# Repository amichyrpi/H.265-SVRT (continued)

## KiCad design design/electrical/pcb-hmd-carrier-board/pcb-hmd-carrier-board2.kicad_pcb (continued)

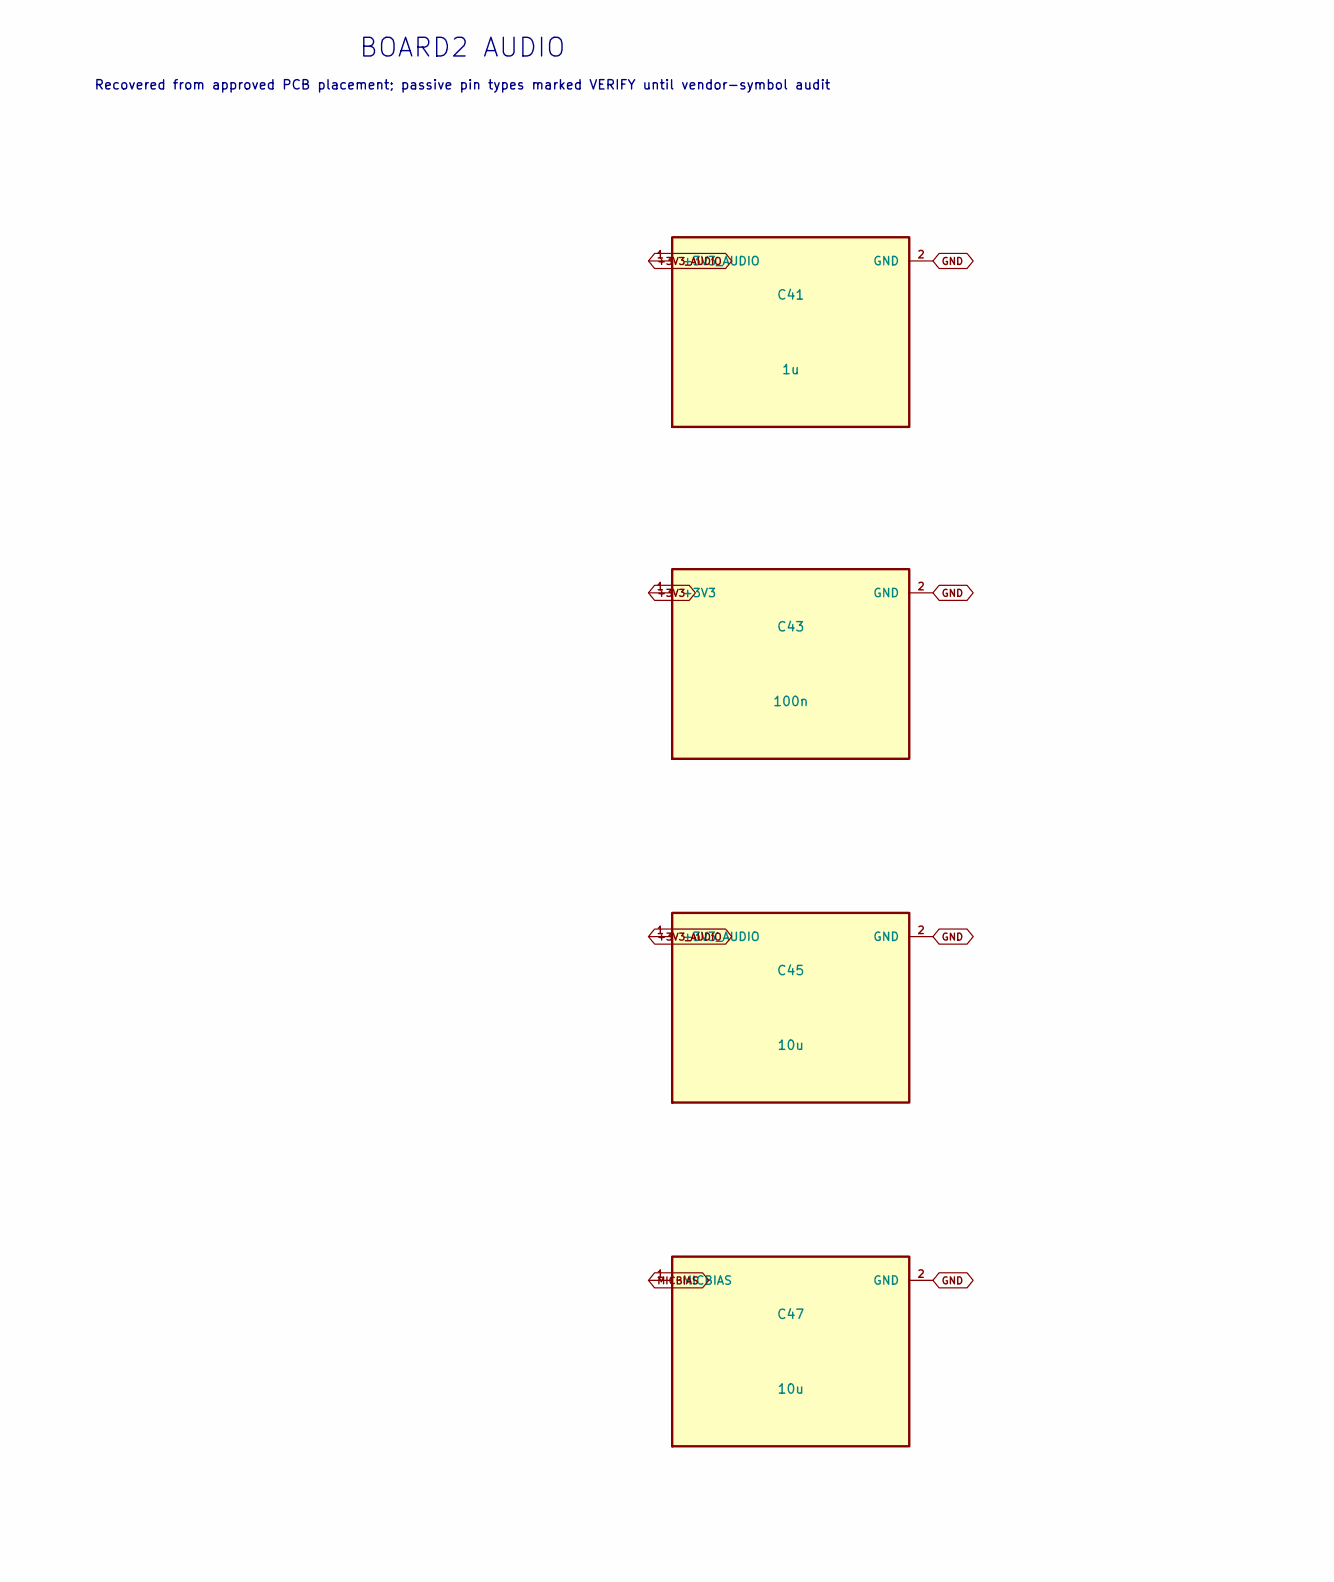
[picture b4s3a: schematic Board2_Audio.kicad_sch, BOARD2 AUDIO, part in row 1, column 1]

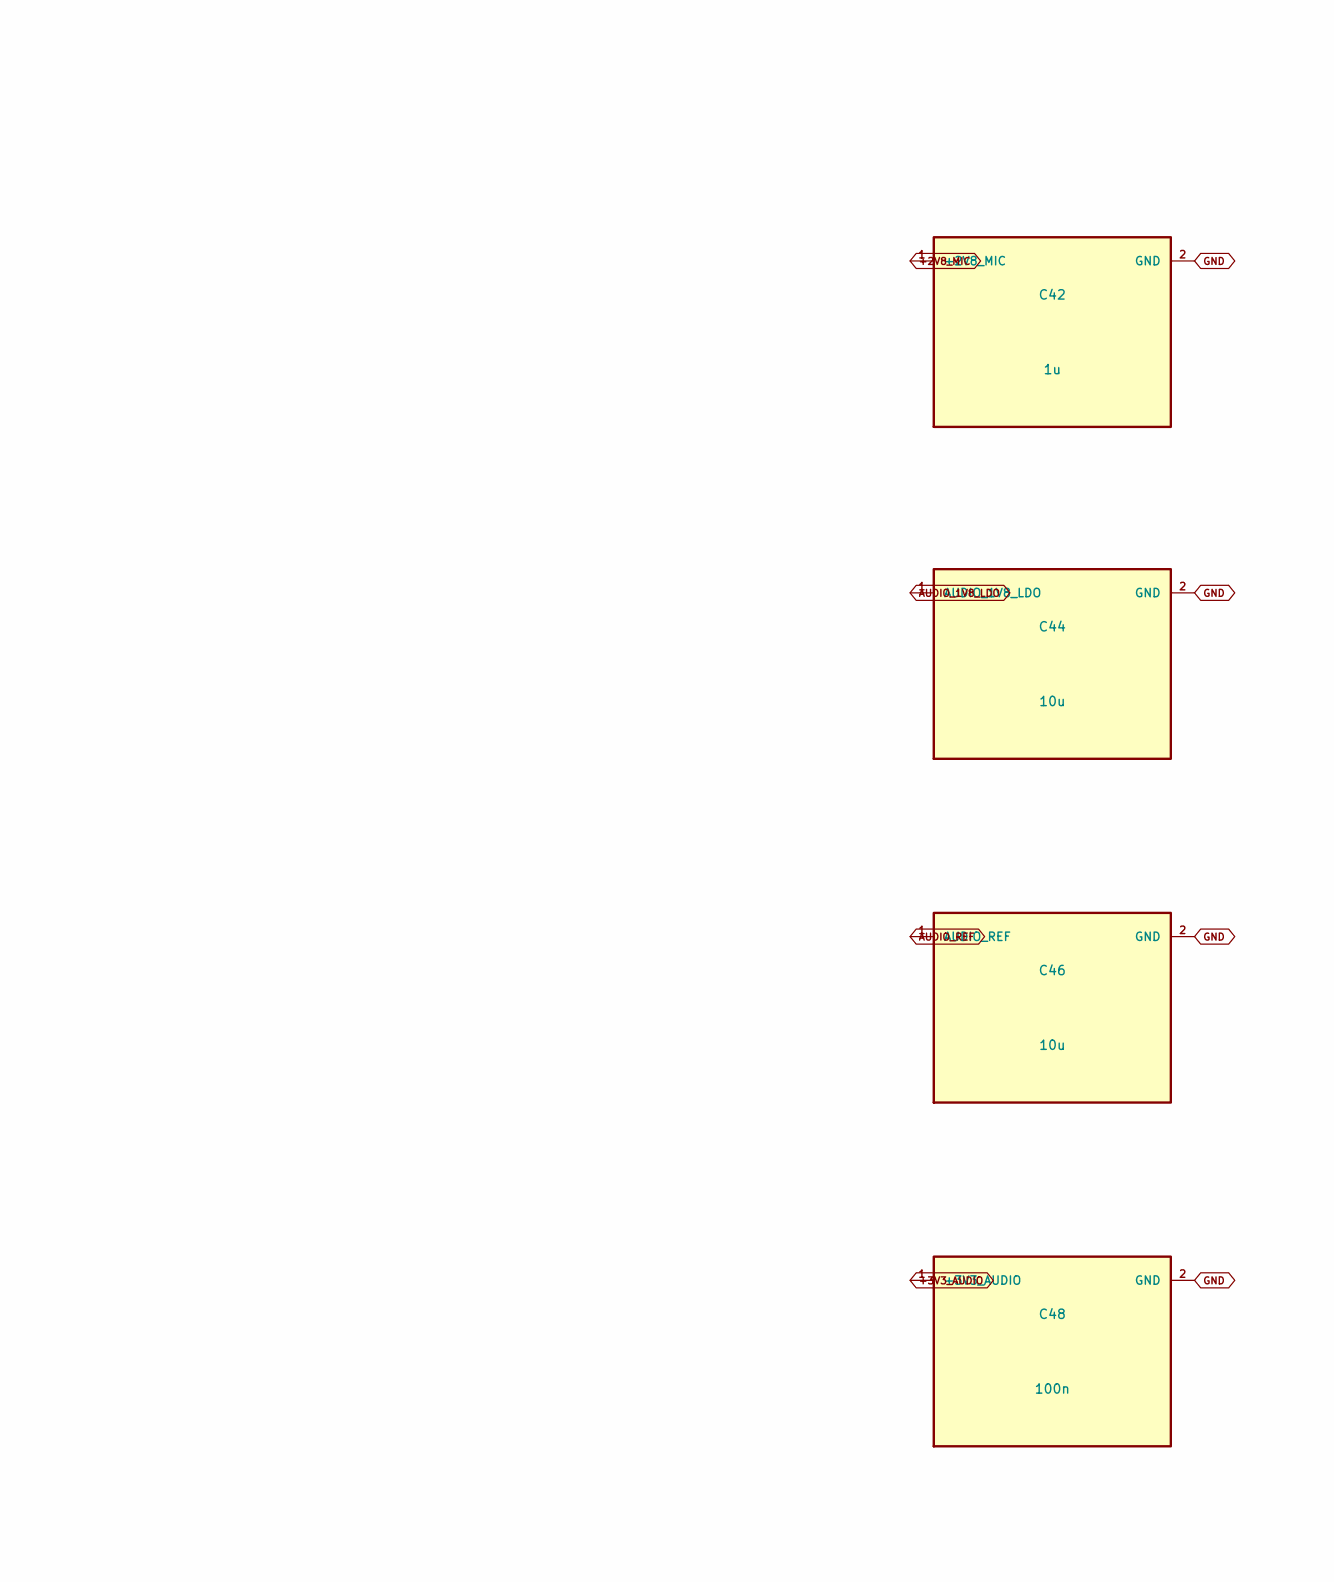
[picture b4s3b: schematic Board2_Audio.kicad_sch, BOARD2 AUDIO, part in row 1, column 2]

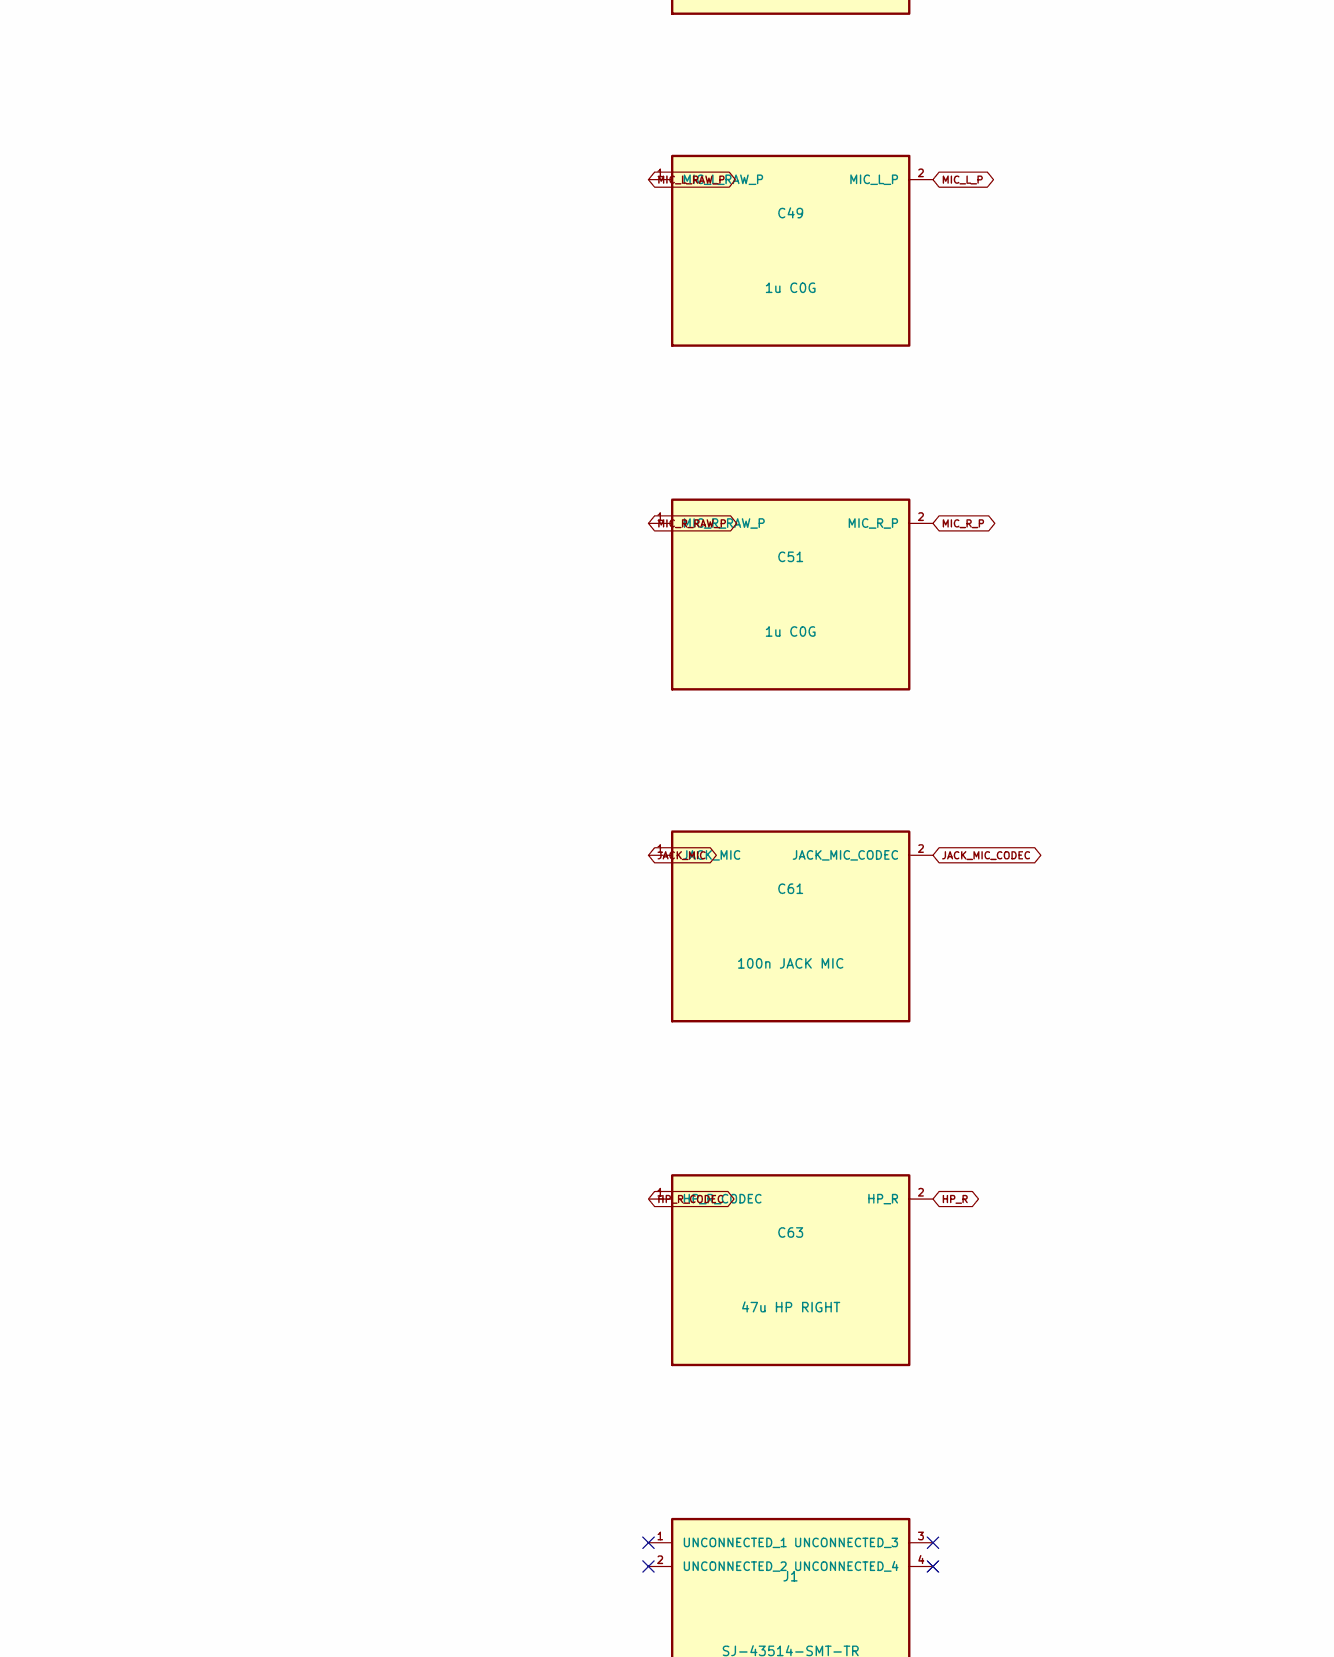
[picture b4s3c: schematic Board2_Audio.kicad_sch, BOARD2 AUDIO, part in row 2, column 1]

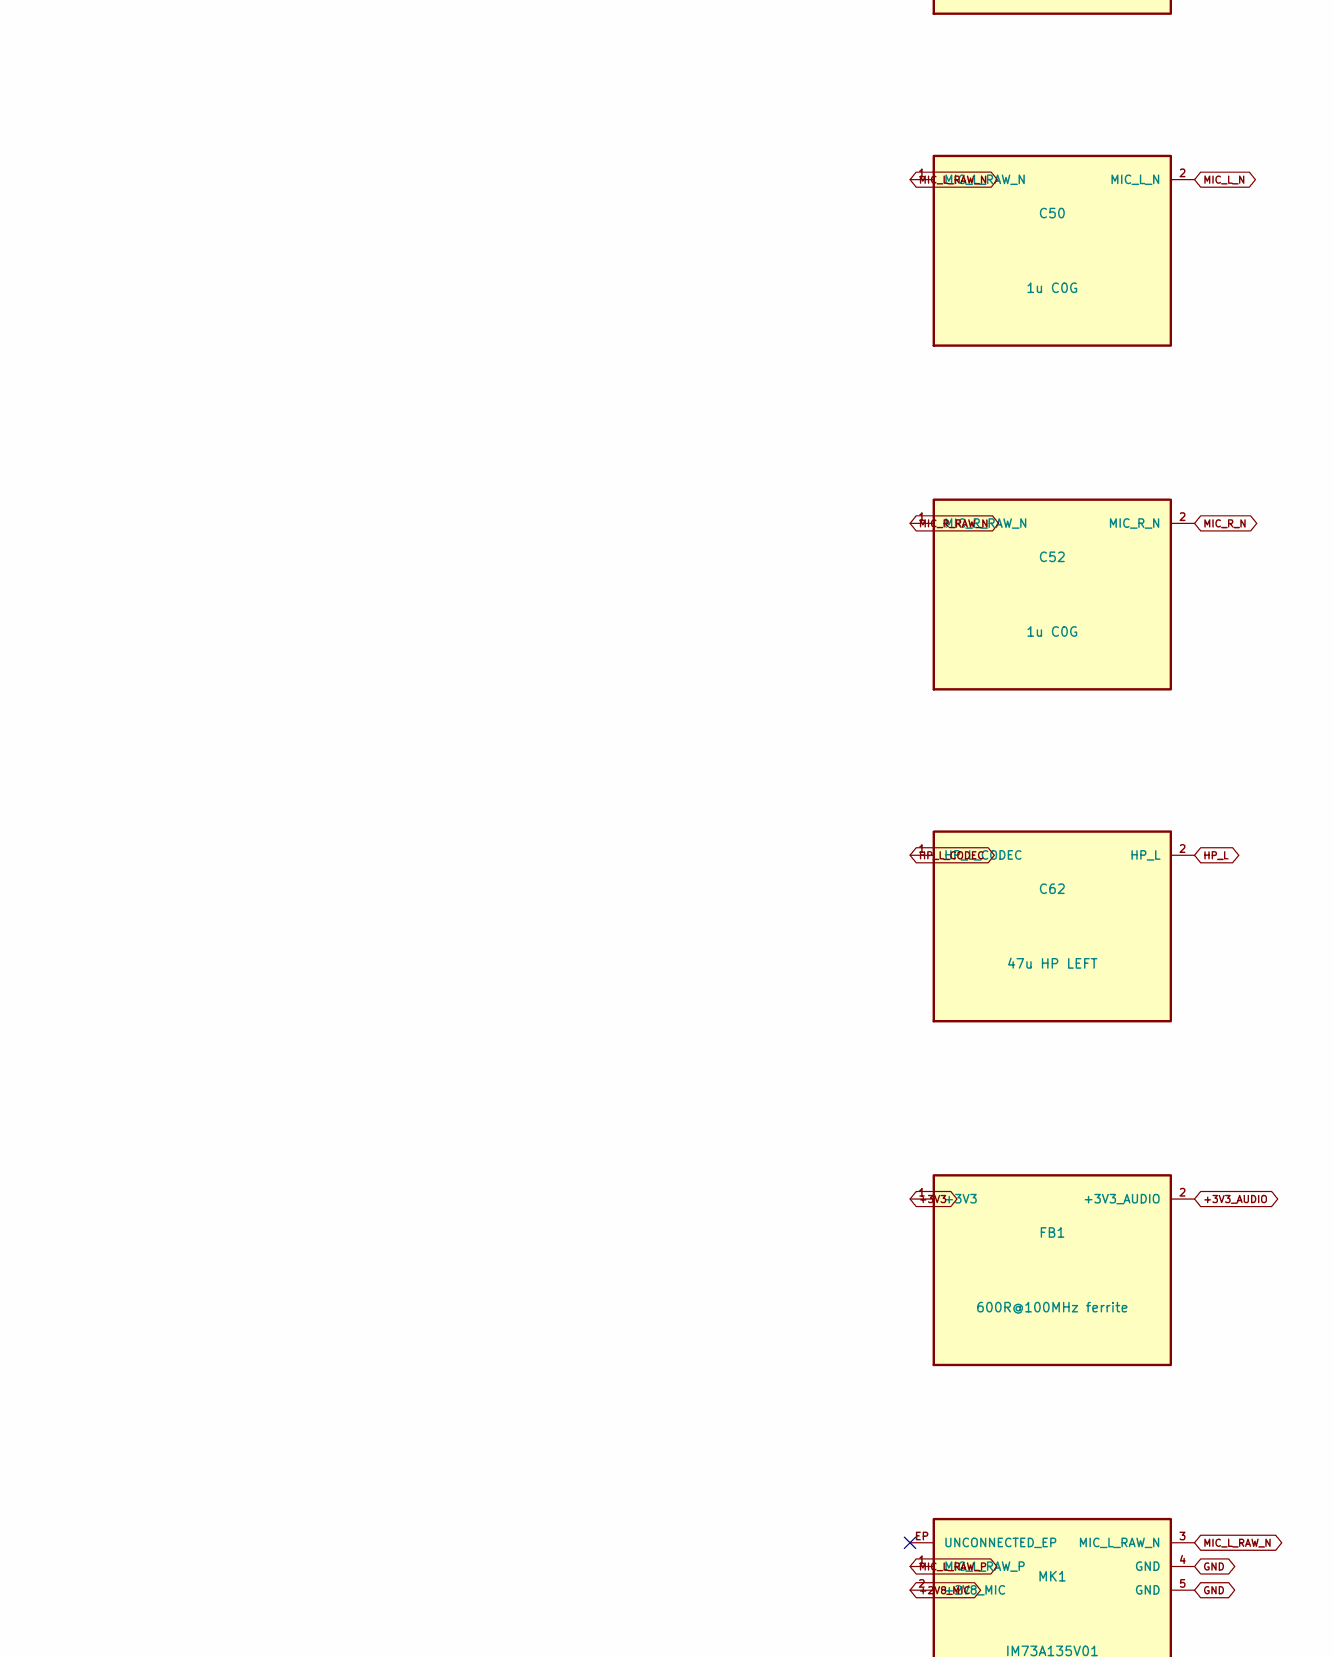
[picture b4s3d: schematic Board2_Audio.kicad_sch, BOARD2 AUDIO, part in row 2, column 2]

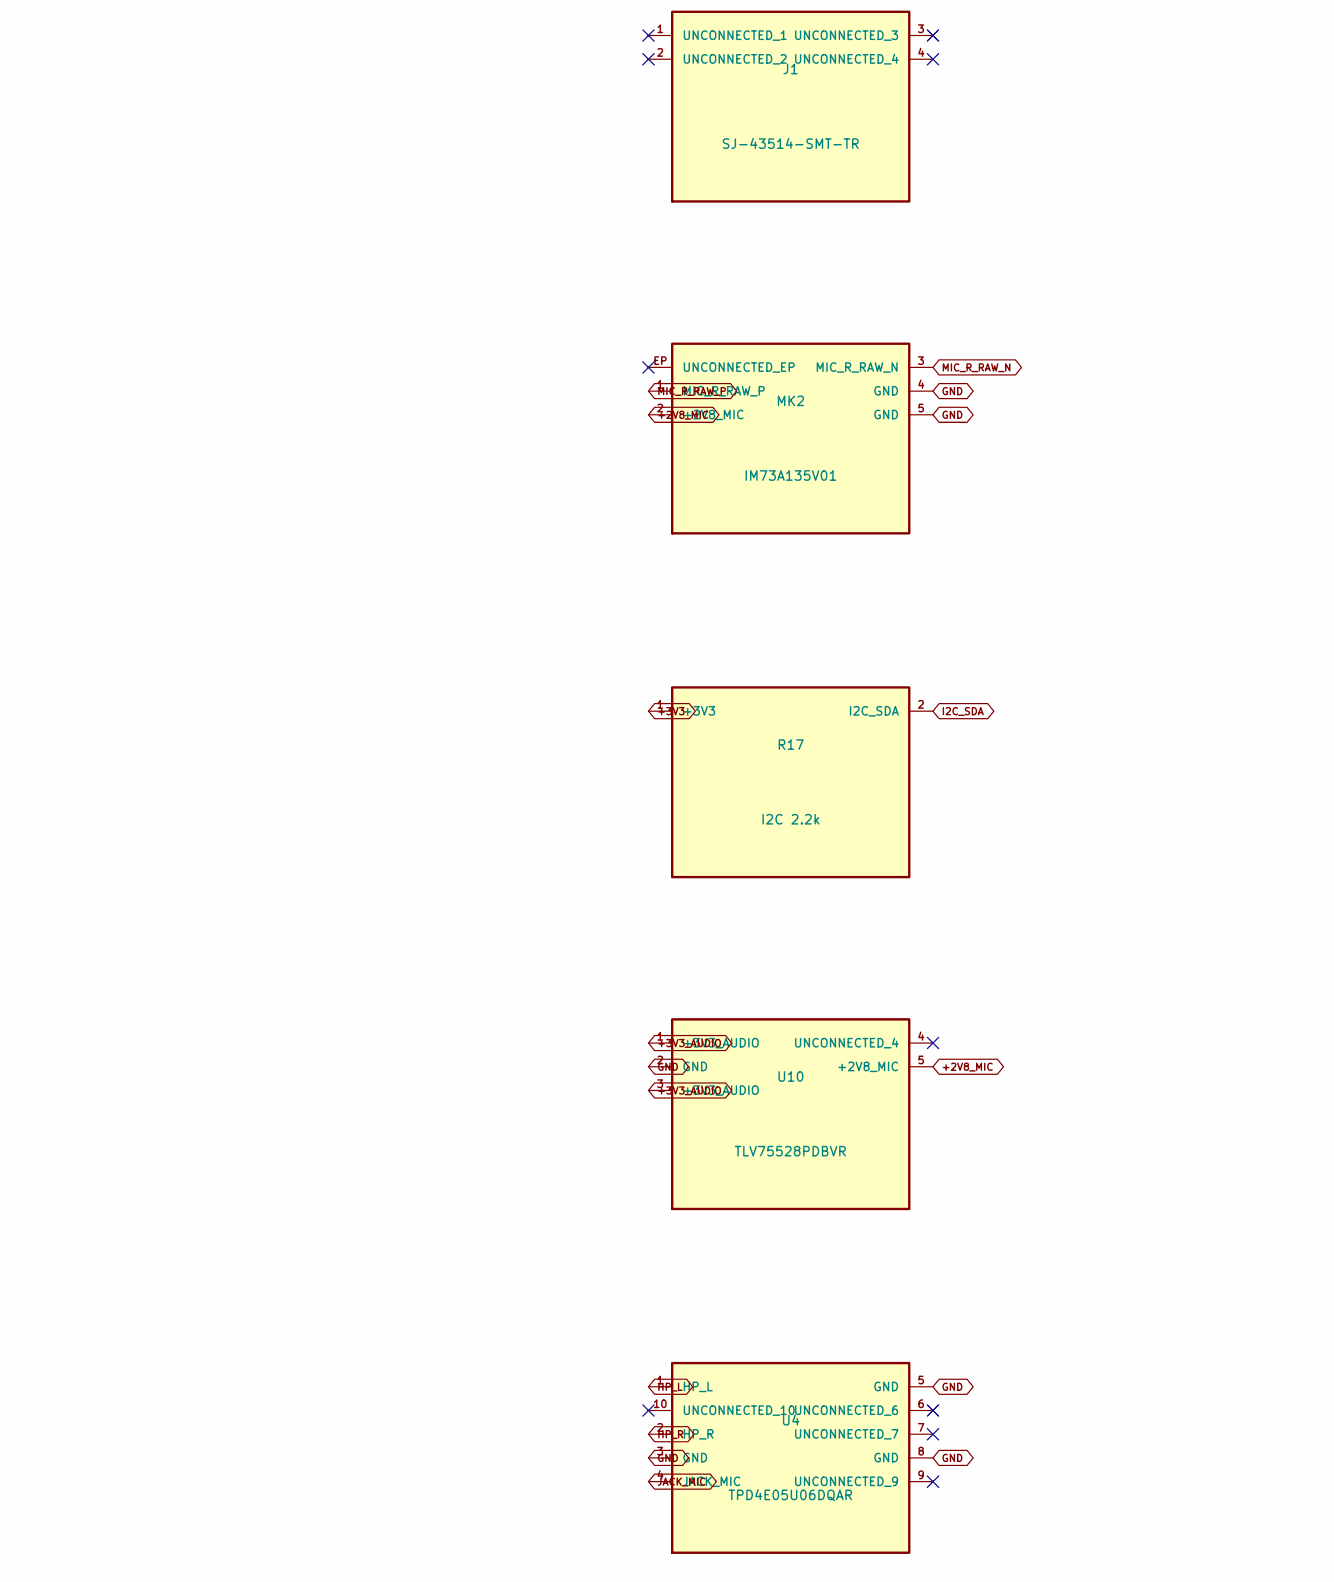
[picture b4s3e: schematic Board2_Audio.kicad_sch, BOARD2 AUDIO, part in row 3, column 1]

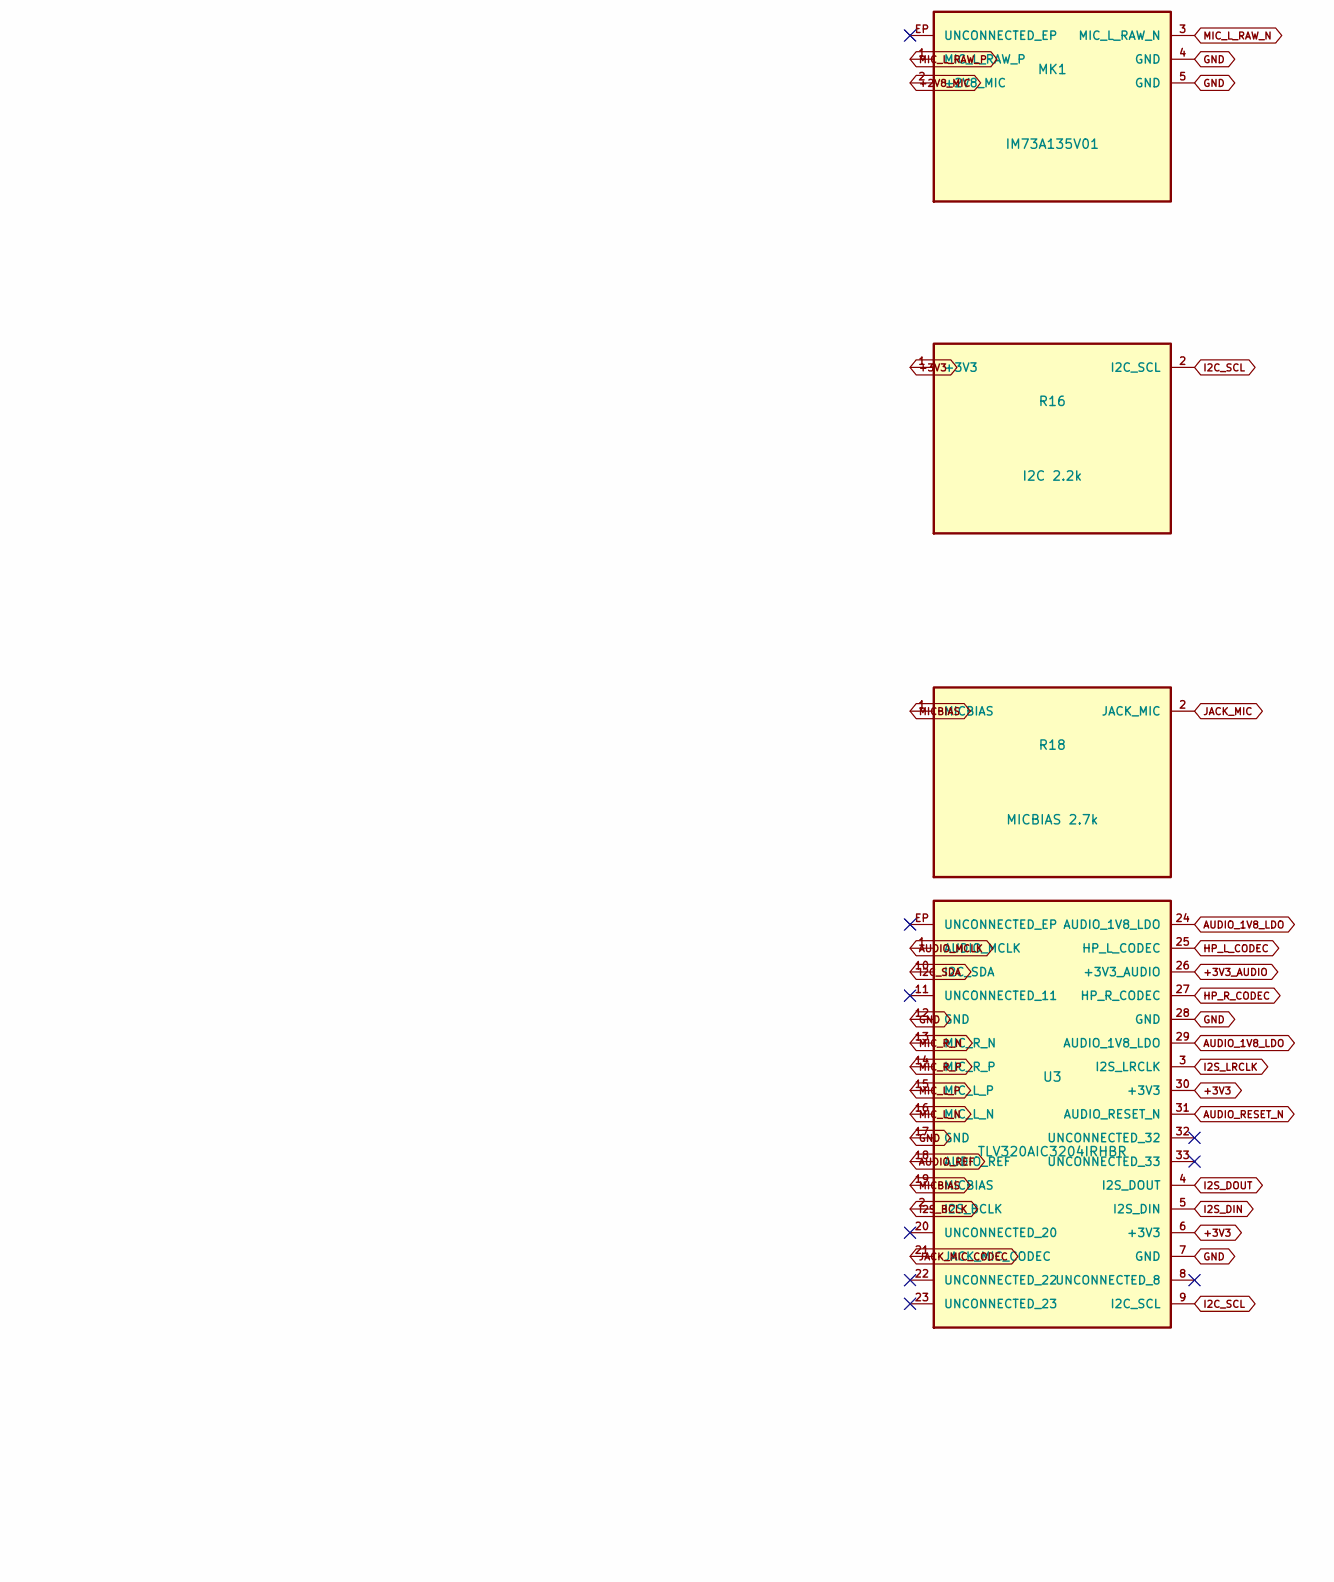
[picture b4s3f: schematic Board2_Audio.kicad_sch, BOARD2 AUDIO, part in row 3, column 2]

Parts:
C41, C42: 1u; C_0402_1005Metric
C43, C48: 100n; C_0402_1005Metric
C44, C45, C46, C47: 10u; C_0402_1005Metric
C49, C50, C51, C52: 1u C0G; C_0402_1005Metric
C61: 100n JACK MIC; C_0402_1005Metric
C62: 47u HP LEFT; C_0603_1608Metric
C63: 47u HP RIGHT; C_0603_1608Metric
FB1: 600R@100MHz ferrite; L_0603_1608Metric
J1: SJ-43514-SMT-TR; SameSky_SJ-43514-SMT-TR
MK1, MK2: IM73A135V01; Infineon_PG-LLGA-5-2
R16, R17: I2C 2.2k; R_0402_1005Metric
R18: MICBIAS 2.7k; R_0402_1005Metric
U3: TLV320AIC3204IRHBR; Texas_RHB0032M_VQFN-32-1EP_5x5mm_P0.5mm_EP2.1x2.1mm_Thermal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
U4: TPD4E05U06DQAR; USON-10_2.5x1.0mm_P0.5mm
U10: TLV75528PDBVR; SOT-23-5

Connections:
+2V8_MIC: C42.1 (+2V8_MIC), MK1.2 (+2V8_MIC), MK2.2 (+2V8_MIC), U10.5 (+2V8_MIC)
+3V3: C43.1 (+3V3), FB1.1 (+3V3), R16.1 (+3V3), R17.1 (+3V3), U3.6 (+3V3), U3.30 (+3V3); also elsewhere on the board
+3V3_AUDIO: C41.1 (+3V3_AUDIO), C45.1 (+3V3_AUDIO), C48.1 (+3V3_AUDIO), FB1.2 (+3V3_AUDIO), U3.26 (+3V3_AUDIO), U10.1 (+3V3_AUDIO), U10.3 (+3V3_AUDIO)
AUDIO_1V8_LDO: C44.1 (AUDIO_1V8_LDO), U3.24 (AUDIO_1V8_LDO), U3.29 (AUDIO_1V8_LDO)
AUDIO_MCLK: U3.1 (AUDIO_MCLK); also elsewhere on the board
AUDIO_REF: C46.1 (AUDIO_REF), U3.18 (AUDIO_REF)
AUDIO_RESET_N: U3.31 (AUDIO_RESET_N); also elsewhere on the board
GND: C41.2 (GND), C42.2 (GND), C43.2 (GND), C44.2 (GND), C45.2 (GND), C46.2 (GND), C47.2 (GND), C48.2 (GND), MK1.4 (GND), MK1.5 (GND), MK2.4 (GND), MK2.5 (GND), U3.7 (GND), U3.12 (GND), U3.17 (GND), U3.28 (GND), U4.3 (GND), U4.5 (GND), U4.8 (GND), U10.2 (GND); also elsewhere on the board
HP_L: C62.2 (HP_L), U4.1 (HP_L)
HP_L_CODEC: C62.1 (HP_L_CODEC), U3.25 (HP_L_CODEC)
HP_R: C63.2 (HP_R), U4.2 (HP_R)
HP_R_CODEC: C63.1 (HP_R_CODEC), U3.27 (HP_R_CODEC)
I2C_SCL: R16.2 (I2C_SCL), U3.9 (I2C_SCL); also elsewhere on the board
I2C_SDA: R17.2 (I2C_SDA), U3.10 (I2C_SDA); also elsewhere on the board
I2S_BCLK: U3.2 (I2S_BCLK); also elsewhere on the board
I2S_DIN: U3.5 (I2S_DIN); also elsewhere on the board
I2S_DOUT: U3.4 (I2S_DOUT); also elsewhere on the board
I2S_LRCLK: U3.3 (I2S_LRCLK); also elsewhere on the board
JACK_MIC: C61.1 (JACK_MIC), R18.2 (JACK_MIC), U4.4 (JACK_MIC)
JACK_MIC_CODEC: C61.2 (JACK_MIC_CODEC), U3.21 (JACK_MIC_CODEC)
MICBIAS: C47.1 (MICBIAS), R18.1 (MICBIAS), U3.19 (MICBIAS)
MIC_L_N: C50.2 (MIC_L_N), U3.16 (MIC_L_N)
MIC_L_P: C49.2 (MIC_L_P), U3.15 (MIC_L_P)
MIC_L_RAW_N: C50.1 (MIC_L_RAW_N), MK1.3 (MIC_L_RAW_N)
MIC_L_RAW_P: C49.1 (MIC_L_RAW_P), MK1.1 (MIC_L_RAW_P)
MIC_R_N: C52.2 (MIC_R_N), U3.13 (MIC_R_N)
MIC_R_P: C51.2 (MIC_R_P), U3.14 (MIC_R_P)
MIC_R_RAW_N: C52.1 (MIC_R_RAW_N), MK2.3 (MIC_R_RAW_N)
MIC_R_RAW_P: C51.1 (MIC_R_RAW_P), MK2.1 (MIC_R_RAW_P)

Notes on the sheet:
BOARD2 AUDIO
Recovered from approved PCB placement; passive pin types marked VERIFY until vendor-symbol audit
